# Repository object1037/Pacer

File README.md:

# Pacer

Runs an automatic Pomodoro Technique cycle upon powering on.

## How It Works

https://github.com/user-attachments/assets/2add35af-41f7-42f3-8dcc-8eead1801370

Executes a repeating 4-set cycle:

- **Standard Sets (Sets 1–3)**
  - Focus: 25 minutes
  - Break: 5 minutes
- **4th Set**
  - Focus: 25 minutes
  - **Long Break**: 30 minutes

*Note: After the 30-minute long break finishes, the cycle automatically resets to Set 1.*

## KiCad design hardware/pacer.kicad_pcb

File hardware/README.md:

# Pacer hardware

* [jlcpcb/production_files](jlcpcb/production_files): Production files (Gerber + Assembly)
* [case](case): Case 3D data
* [BOM_ext.md](BOM_ext.md): Extra parts for hand-soldering and assembly

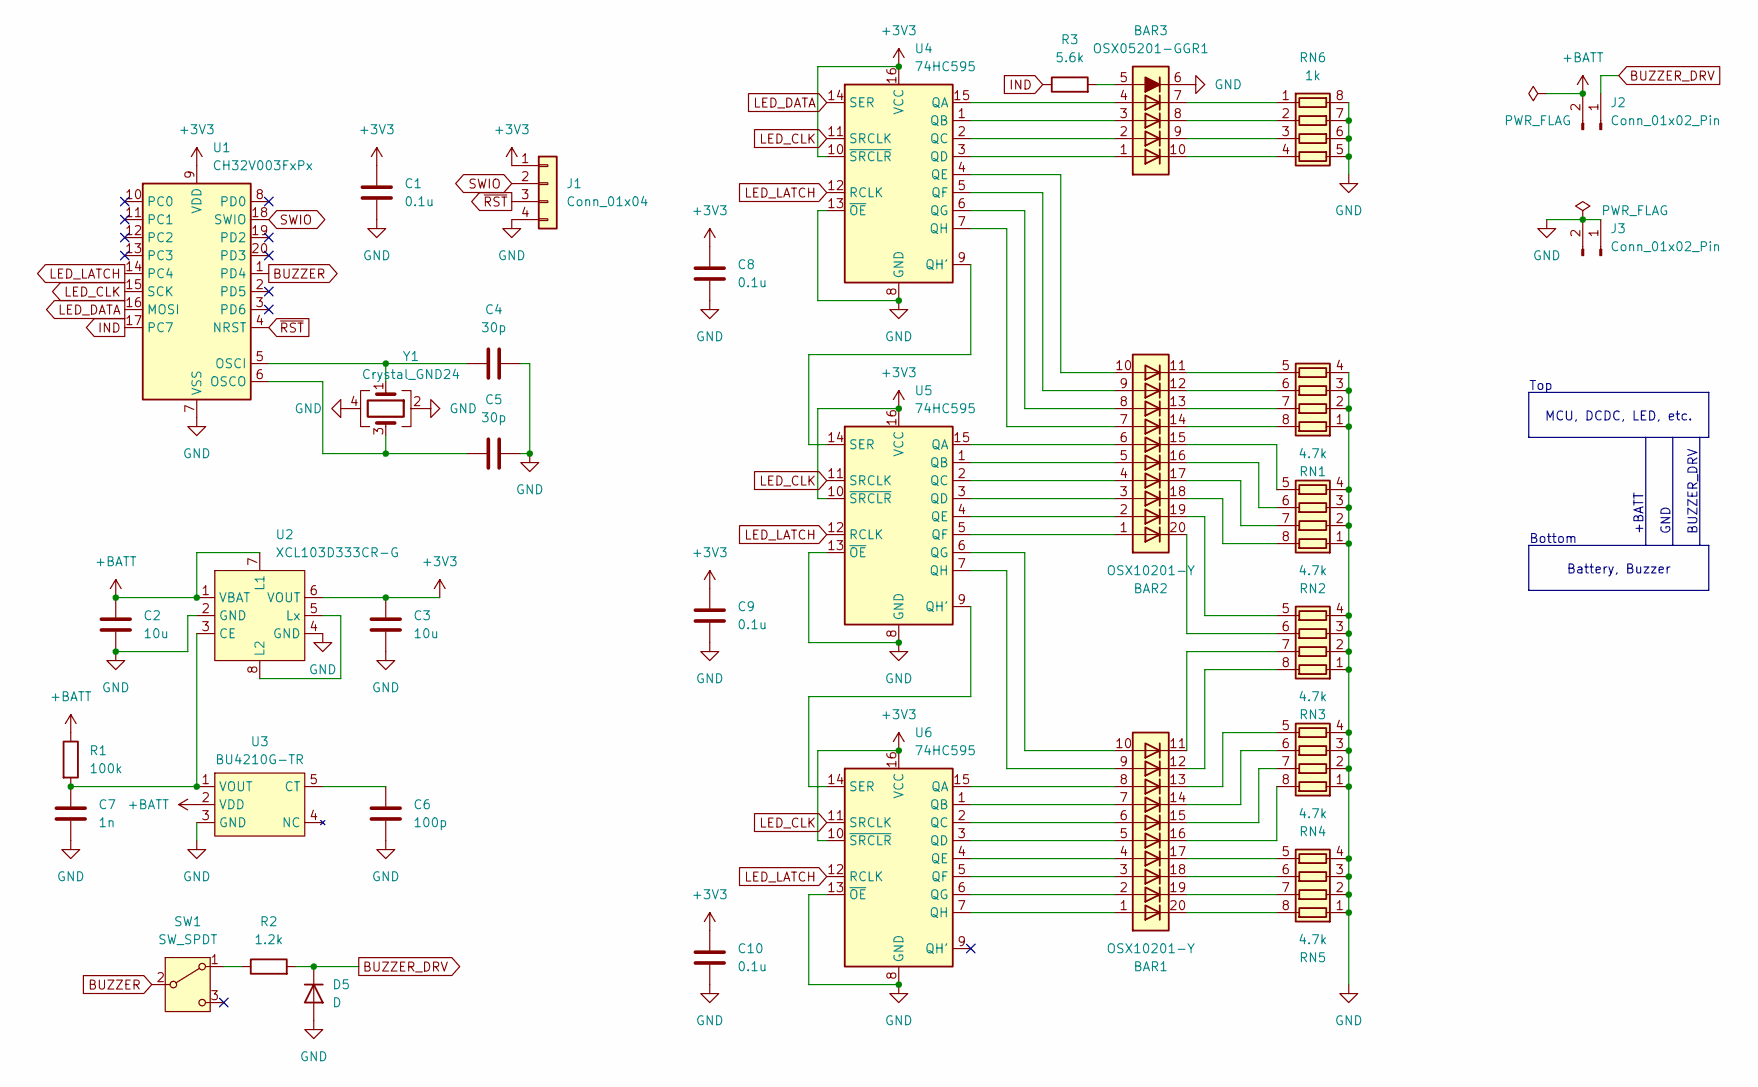
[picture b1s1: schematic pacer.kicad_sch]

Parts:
BAR1, BAR2: OSX10201-Y; HDSP-4840
BAR3: OSX05201-GGR1
C1, C8, C9, C10: 0.1u; C_0402_1005Metric_Pad0.74x0.62mm_HandSolder
C2, C3: 10u; C_0603_1608Metric_Pad1.08x0.95mm_HandSolder
C4, C5: 30p; C_0603_1608Metric_Pad1.08x0.95mm_HandSolder
C6: 100p; C_0402_1005Metric_Pad0.74x0.62mm_HandSolder
C7: 1n; C_0402_1005Metric_Pad0.74x0.62mm_HandSolder
D5: D; SOD-123FL
J1: Conn_01x04; PinHeader_1x04_P2.54mm_Vertical
J2, J3: Conn_01x02_Pin; PinHeader_1x02_P2.54mm_Vertical
R1: 100k; R_0603_1608Metric_Pad0.98x0.95mm_HandSolder
R2: 1.2k; R_0603_1608Metric_Pad0.98x0.95mm_HandSolder
R3: 5.6k; R_0603_1608Metric_Pad0.98x0.95mm_HandSolder
RN1, RN2, RN3, RN4, RN5: 4.7k; R_Array_Convex_4x0603
RN6: 1k; R_Array_Convex_4x0603
SW1: SW_SPDT; SW_SPDT_IS-1245T
U1: CH32V003FxPx; TSSOP-20_4.4x6.5mm_P0.65mm
U2: XCL103D333CR-G; CL2025-02
U3: BU4210G-TR; SSOP5
U4, U5, U6: 74HC595; SOIC-16_3.9x9.9mm_P1.27mm
Y1: Crystal_GND24; Crystal_SMD_3225-4Pin_3.2x2.5mm

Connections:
+3V3: C1.1, C3.1, C8.1, C9.1, C10.1, J1.1, U1.9 (VDD), U2.6 (VOUT), U4.10 (~SRCLR), U4.16 (VCC), U5.10 (~SRCLR), U5.16 (VCC), U6.10 (~SRCLR), U6.16 (VCC)
+BATT: C2.1, J2.2, R1.1, U2.1 (VBAT), U2.7 (L1), U3.2 (VDD)
BUZZER: SW1.2 (B), U1.1 (PD4)
BUZZER_DRV: D5.1 (K), J2.1, R2.2
GND: BAR3.6 (K), C1.2, C2.2, C3.2, C4.1, C5.2, C6.2, C7.2, C8.2, C9.2, C10.2, D5.2 (A), J1.4, J3.1, J3.2, RN1.1 (R1.1), RN1.2 (R2.1), RN1.3 (R3.1), RN1.4 (R4.1), RN2.1 (R1.1), RN2.2 (R2.1), RN2.3 (R3.1), RN2.4 (R4.1), RN3.1 (R1.1), RN3.2 (R2.1), RN3.3 (R3.1), RN3.4 (R4.1), RN4.1 (R1.1), RN4.2 (R2.1), RN4.3 (R3.1), RN4.4 (R4.1), RN5.1 (R1.1), RN5.2 (R2.1), RN5.3 (R3.1), RN5.4 (R4.1), RN6.5 (R4.2), RN6.6 (R3.2), RN6.7 (R2.2), RN6.8 (R1.2), U1.7 (VSS), U2.2 (GND), U2.4 (GND), U3.3 (GND), U4.8 (GND), U4.13 (~OE), U5.8 (GND), U5.13 (~OE), U6.8 (GND), U6.13 (~OE), Y1.2, Y1.4
IND: R3.1, U1.17 (PC7)
LED_CLK: U1.15 (SCK), U4.11 (SRCLK), U5.11 (SRCLK), U6.11 (SRCLK)
LED_DATA: U1.16 (MOSI), U4.14 (SER)
LED_LATCH: U1.14 (PC4), U4.12 (RCLK), U5.12 (RCLK), U6.12 (RCLK)
unnamed: BAR3.5 (A), R3.2
unnamed: BAR2.14 (K), RN1.8 (R1.2)
unnamed: BAR2.13 (K), RN1.7 (R2.2)
unnamed: BAR2.12 (K), RN1.6 (R3.2)
unnamed: BAR2.11 (K), RN1.5 (R4.2)
unnamed: BAR2.18 (K), RN2.8 (R1.2)
unnamed: BAR2.17 (K), RN2.7 (R2.2)
unnamed: BAR2.16 (K), RN2.6 (R3.2)
unnamed: BAR2.15 (K), RN2.5 (R4.2)
unnamed: BAR1.12 (K), RN3.8 (R1.2)
unnamed: BAR1.11 (K), RN3.7 (R2.2)
unnamed: BAR2.20 (K), RN3.6 (R3.2)
unnamed: BAR2.19 (K), RN3.5 (R4.2)
unnamed: BAR1.16 (K), RN4.8 (R1.2)
unnamed: BAR1.15 (K), RN4.7 (R2.2)
unnamed: BAR1.14 (K), RN4.6 (R3.2)
unnamed: BAR1.13 (K), RN4.5 (R4.2)
unnamed: BAR1.20 (K), RN5.8 (R1.2)
unnamed: BAR1.19 (K), RN5.7 (R2.2)
unnamed: BAR1.18 (K), RN5.6 (R3.2)
unnamed: BAR1.17 (K), RN5.5 (R4.2)
unnamed: BAR3.7 (K), RN6.1 (R1.1)
unnamed: BAR3.8 (K), RN6.2 (R2.1)
unnamed: BAR3.9 (K), RN6.3 (R3.1)
unnamed: BAR3.10 (K), RN6.4 (R4.1)
unnamed: R2.1, SW1.1 (A)
unnamed: C4.2, U1.5 (OSCI), Y1.1
unnamed: C5.1, U1.6 (OSCO), Y1.3
unnamed: C7.1, R1.2, U2.3 (CE), U3.1 (VOUT)
unnamed: U2.5 (Lx), U2.8 (L2)
unnamed: C6.1, U3.5 (CT)
unnamed: BAR3.4 (A), U4.15 (QA)
unnamed: BAR3.3 (A), U4.1 (QB)
unnamed: BAR3.2 (A), U4.2 (QC)
unnamed: BAR3.1 (A), U4.3 (QD)
unnamed: BAR2.10 (A), U4.4 (QE)
unnamed: BAR2.9 (A), U4.5 (QF)
unnamed: BAR2.8 (A), U4.6 (QG)
unnamed: U4.9 (QH'), U5.14 (SER)
unnamed: BAR2.7 (A), U4.7 (QH)
unnamed: BAR2.6 (A), U5.15 (QA)
unnamed: BAR2.5 (A), U5.1 (QB)
unnamed: BAR2.4 (A), U5.2 (QC)
unnamed: BAR2.3 (A), U5.3 (QD)
unnamed: BAR2.2 (A), U5.4 (QE)
unnamed: BAR2.1 (A), U5.5 (QF)
unnamed: BAR1.10 (A), U5.6 (QG)
unnamed: U5.9 (QH'), U6.14 (SER)
unnamed: BAR1.9 (A), U5.7 (QH)
unnamed: BAR1.8 (A), U6.15 (QA)
unnamed: BAR1.7 (A), U6.1 (QB)
unnamed: BAR1.6 (A), U6.2 (QC)
unnamed: BAR1.5 (A), U6.3 (QD)
unnamed: BAR1.4 (A), U6.4 (QE)
unnamed: BAR1.3 (A), U6.5 (QF)
unnamed: BAR1.2 (A), U6.6 (QG)
unnamed: BAR1.1 (A), U6.7 (QH)
SWIO: J1.2, U1.18 (SWIO)
~RST: J1.3, U1.4 (NRST)

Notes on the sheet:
Battery, Buzzer
+BATT
GND
Bottom
MCU, DCDC, LED, etc.
Top
BUZZER_DRV

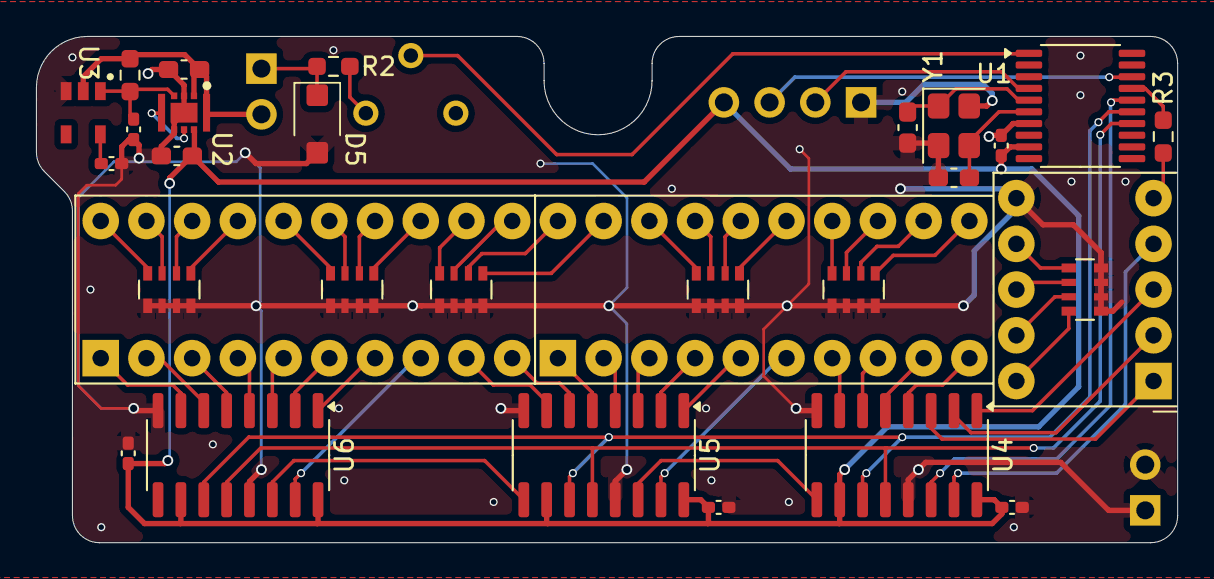
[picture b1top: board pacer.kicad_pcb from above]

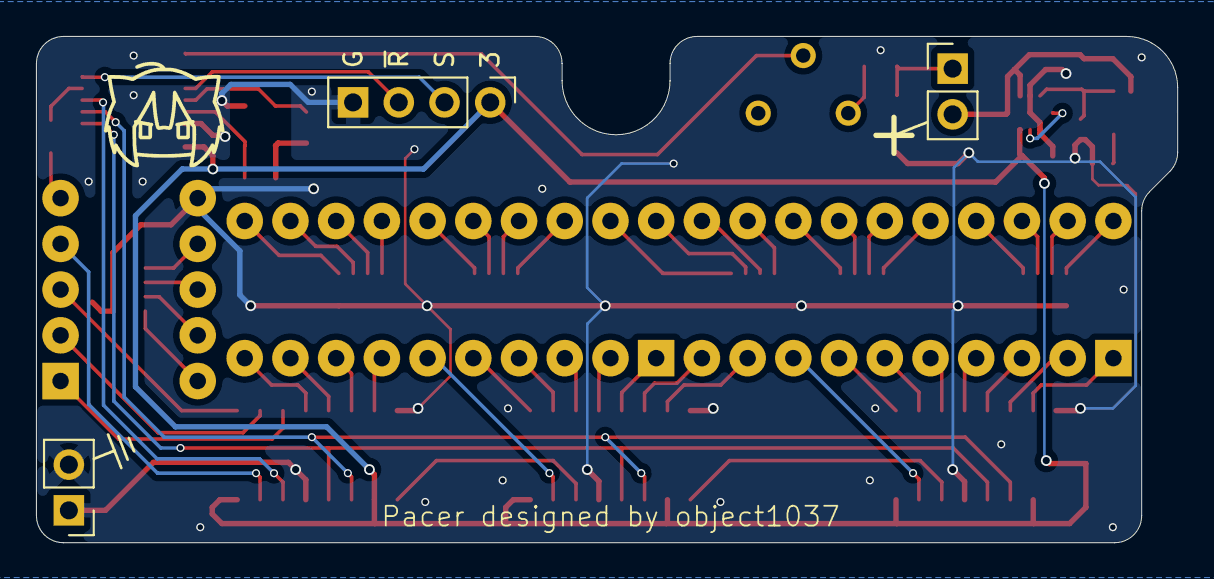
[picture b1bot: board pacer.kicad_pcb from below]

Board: 2 copper layers, 63.4 x 28.1 mm, 34 parts (4 on the bottom side), 68 nets.

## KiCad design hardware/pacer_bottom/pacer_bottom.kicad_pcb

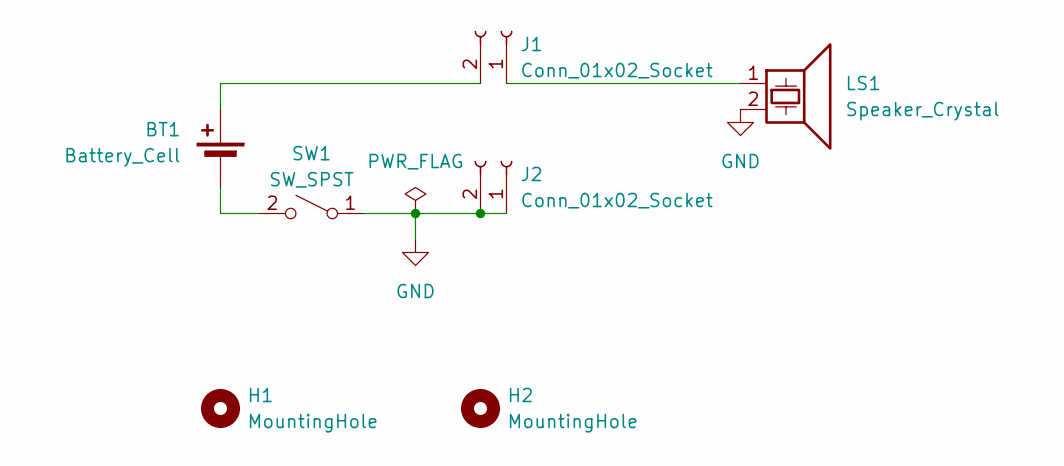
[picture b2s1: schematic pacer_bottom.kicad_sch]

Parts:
BT1: Battery_Cell; BatteryHolder_Keystone_2460_1xAA
H1, H2: MountingHole; MountingHole_2.2mm_M2
J1, J2: Conn_01x02_Socket; PinSocket_1x02_P2.54mm_Vertical
LS1: Speaker_Crystal; buzzer_pkm13
SW1: SW_SPST; DS-850K-S

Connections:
GND: J2.1, J2.2, LS1.2, SW1.1 (A)
unnamed: BT1.1 (+), J1.2
unnamed: BT1.2 (-), SW1.2 (B)
unnamed: J1.1, LS1.1

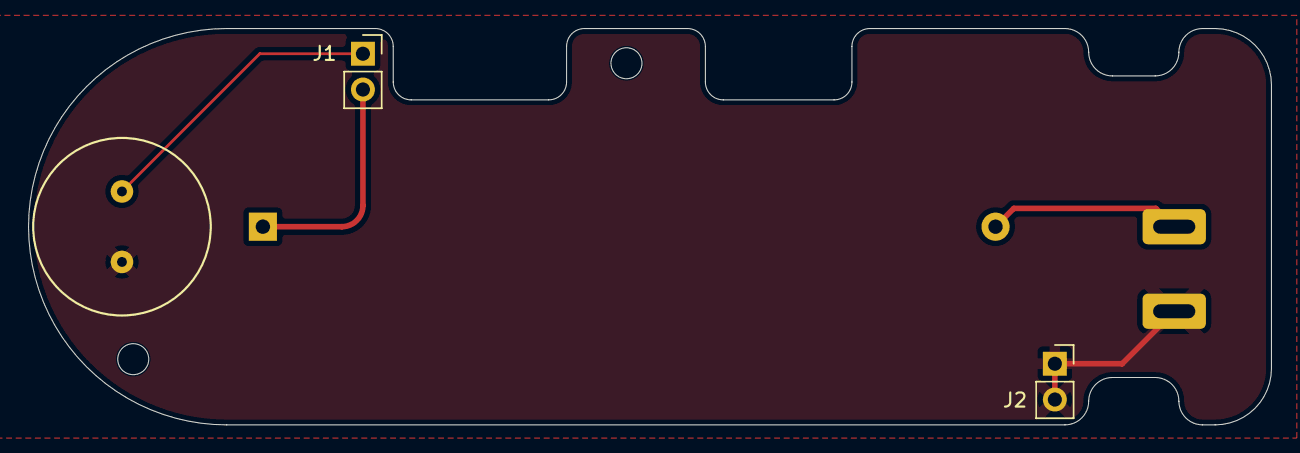
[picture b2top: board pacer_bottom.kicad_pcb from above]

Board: 2 copper layers, 88.2 x 28.1 mm, 7 parts (1 on the bottom side), 4 nets.
